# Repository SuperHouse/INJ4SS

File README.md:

Power-over-Ethernet 4-Channel Midspan Injector (Single Sided)
=============================================================
Copyright 2017 SuperHouse Automation Pty Ltd  
SuperHouse site:  <www.superhouse.tv>  

Trivial board to supply power to 4 remote devices via Ethernet
connections. Has no voltage regulation at all: whatever you plug in will
simply be sent down the wire, no questions asked. Be very, very careful
with this or you may damage your Ethernet device!

Features:

 * 2.1mm DC input jack
 * "Power On" LED.
 * 4 channels (4 inputs, 4 outputs)

More information is available at:

  http://www.superhouse.tv/inj4ss

The "docs" folder within this repository includes a handy copy of the
schematic in PDF format and image(s) of the pcb.

INSTALLATION
------------
The design is saved as an EAGLE project. EAGLE PCB design software is
available from www.cadsoftusa.com free for non-commercial use. To use
this project download it and place the directory containing these files
into the "eagle" directory on your computer. Then open EAGLE and
navigate to the project.

DISTRIBUTION
------------
The specific terms of distribution of this project are governed by the
license referenced below.

LICENSE
-------
Licensed under the TAPR Open Hardware License (www.tapr.org/OHL).
The "license" folder within this repository also contains a copy of
this license in plain text format.

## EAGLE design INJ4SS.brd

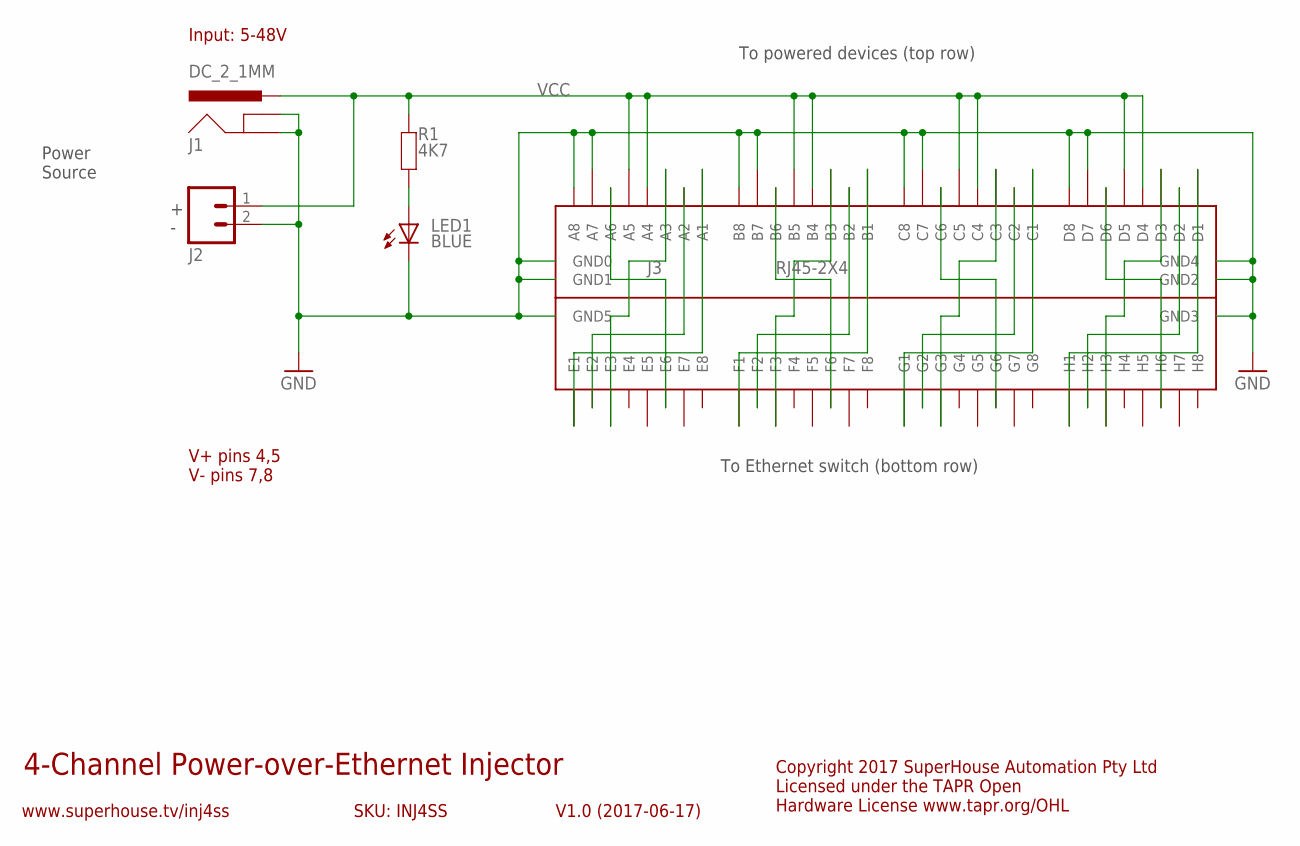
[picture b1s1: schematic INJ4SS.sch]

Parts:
J1: DC_2_1MM; POWER_JACK_PTH
J2: M023.5MM; SCREWTERMINAL-3.5MM-2
J3: RJ45-2X4
LED1: BLUE; LED3MM
R1: 4K7; RES-4

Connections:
GND: J1.GND, J1.GNDBREAK, J2.2, J3.A7, J3.A8, J3.B7, J3.B8, J3.C7, J3.C8, J3.D7, J3.D8, J3.GND0, J3.GND1, J3.GND2, J3.GND3, J3.GND4, J3.GND5, LED1.K (C)
unnamed: J3.B3, J3.F3
unnamed: J3.B6, J3.F6
unnamed: LED1.A, R1.2
unnamed: J3.B1, J3.F1
unnamed: J3.B2, J3.F2
unnamed: J3.C6, J3.G6
unnamed: J3.D6, J3.H6
unnamed: J3.C1, J3.G1
unnamed: J3.C2, J3.G2
unnamed: J3.C3, J3.G3
unnamed: J3.D1, J3.H1
unnamed: J3.D2, J3.H2
unnamed: J3.D3, J3.H3
unnamed: J3.A1, J3.E1
unnamed: J3.A2, J3.E2
unnamed: J3.A3, J3.E3
unnamed: J3.A6, J3.E6
VCC: J1.PWR, J2.1, J3.A4, J3.A5, J3.B4, J3.B5, J3.C4, J3.C5, J3.D4, J3.D5, R1.1

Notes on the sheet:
4-Channel Power-over-Ethernet Injector
V1.0 (2017-06-17)
www.superhouse.tv/inj4ss
SKU: INJ4SS
To Ethernet switch (bottom row)
To powered devices (top row)
Input: 5-48V
V+ pins 4,5 V- pins 7,8
Copyright 2017 SuperHouse Automation Pty Ltd Licensed under the TAPR Open Hardware License www.tapr.org/OHL
Power Source

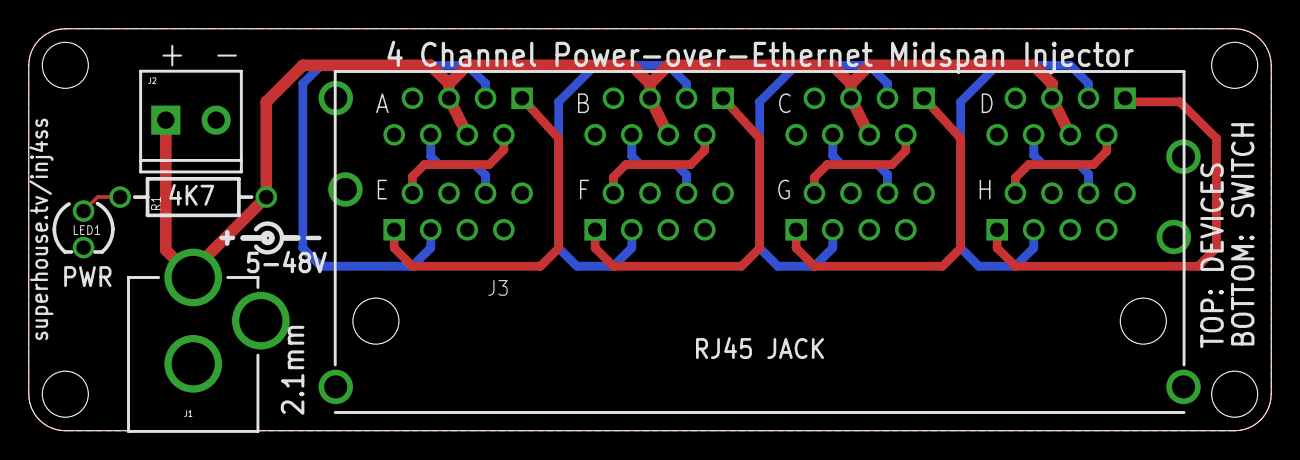
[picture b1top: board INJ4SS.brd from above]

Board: 2 copper layers, 86.4 x 27.9 mm, 5 parts (0 on the bottom side), 19 nets.

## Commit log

2017-07-17 Initial project import for v1.0 release

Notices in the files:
INJ4SS.brd:
(C)2017 SuperHouse Automation Pty Ltd
